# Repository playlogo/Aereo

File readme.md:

# Aereo - CO2 & PM2.5 Air Sensor with custom PCB

A DIY IoT air-quality sensor using a `Senseair S8` for CO2 and a `PMS5003` for particulate matter.

Features:

- ESP32c3 firmware to publish measurements to influxDB
- Custom PCB for easy assembly
- Grafana dashboard to display data

|||
|-|-|
|||

## Tutorial

### Installing InfluxDB & Grafana using docker

1. Clone this repo: `git clone https://github.com/playlogo/Aereo.git`
2. Run `docker compose up -d`

3. Setup Grafana at: `http://<ip>:3000`
4. Setup InfluxDB at: `http://<ip>:8086`

5. Follow [this guide](https://www.influxdata.com/blog/getting-started-influxdb-grafana/) to add InfluxDB as a Datasource to Grafana
6. Import the Grafana dashboard:
    - Create a new empty dashboard: `Home` -> `Dashboards` -> `New`
    - Click the little gear icon to get to the `Dashboard Settings`
    - Go to the `JSON Model` tab
    - Copy the contents of the `grafana_dashboard.json` file and paste them into the editor
    - Hit `Save Changes` and reload - voilà (you might still need to change the Datasource of each Graph to the one you just created)

Optional: Create your own dashboard following the guide linked above (don't forget to hit save!)

### Flashing the ESP32c3

1. Open `.vscode/Aereo.code-workspace` using VSCode, make sure you have [PlatformIO](https://platformio.org/install/ide?install=vscode) installed and setup
2. Create `Aereo/src/secrets.h` with the following content:

```cpp
#define WIFI_SSID "NEIGHBORS_WIFI"
#define WIFI_PASSWORD "123456789"

#define INFLUXDB_URL "http://192.168.178.64:8086/"
#define INFLUXDB_TOKEN "token please" // Guide: https://docs.influxdata.com/influxdb3/cloud-serverless/admin/tokens/create-token/
#define INFLUXDB_ORG "bumble"
#define INFLUXDB_BUCKET "aereo" // Guide: https://docs.influxdata.com/influxdb/v2/admin/buckets/create-bucket/
```

3. Build & Upload to the ESP32c3: `CTRL+P` -> `PlatformIO: Upload`
4. The neopixel should blink blue while the ESP connects to wifi, when connected it should turn off - if it continues showing one static color, one of the sensors has not been detected -> Check serial output: `CTRL+P` -> `PlatformIO: Upload and Monitor`

## Hardware

Required components:

- `ENS160-AHT21`: Temp + TVOC sensor ~4€ on aliexpress
- `Senseair S8`: [NDIR](https://en.wikipedia.org/wiki/Nondispersive_infrared_sensor) CO2 Sensor ~20€ on aliexpress
- `PMS5003`:  Particulate matter sensor ~14€ on aliexpress
- `WeAct ESP32C3 CoreBoard`: ~4€ on aliexpress
- `SK6812 mini e`: 1x ARGB status LED ~3€ on aliexpress (for 100pcs)

PCB:

- Houses two independent projects to save costs, the right half can simply be ignored
- Exposed connectors:
  - 2x 3 Pin (5V, GND, Data)
  - 2x 4 Pin (5V, GND, Data, Data)
  - 3x Power (5V, GND)
- Size: 100x100mm

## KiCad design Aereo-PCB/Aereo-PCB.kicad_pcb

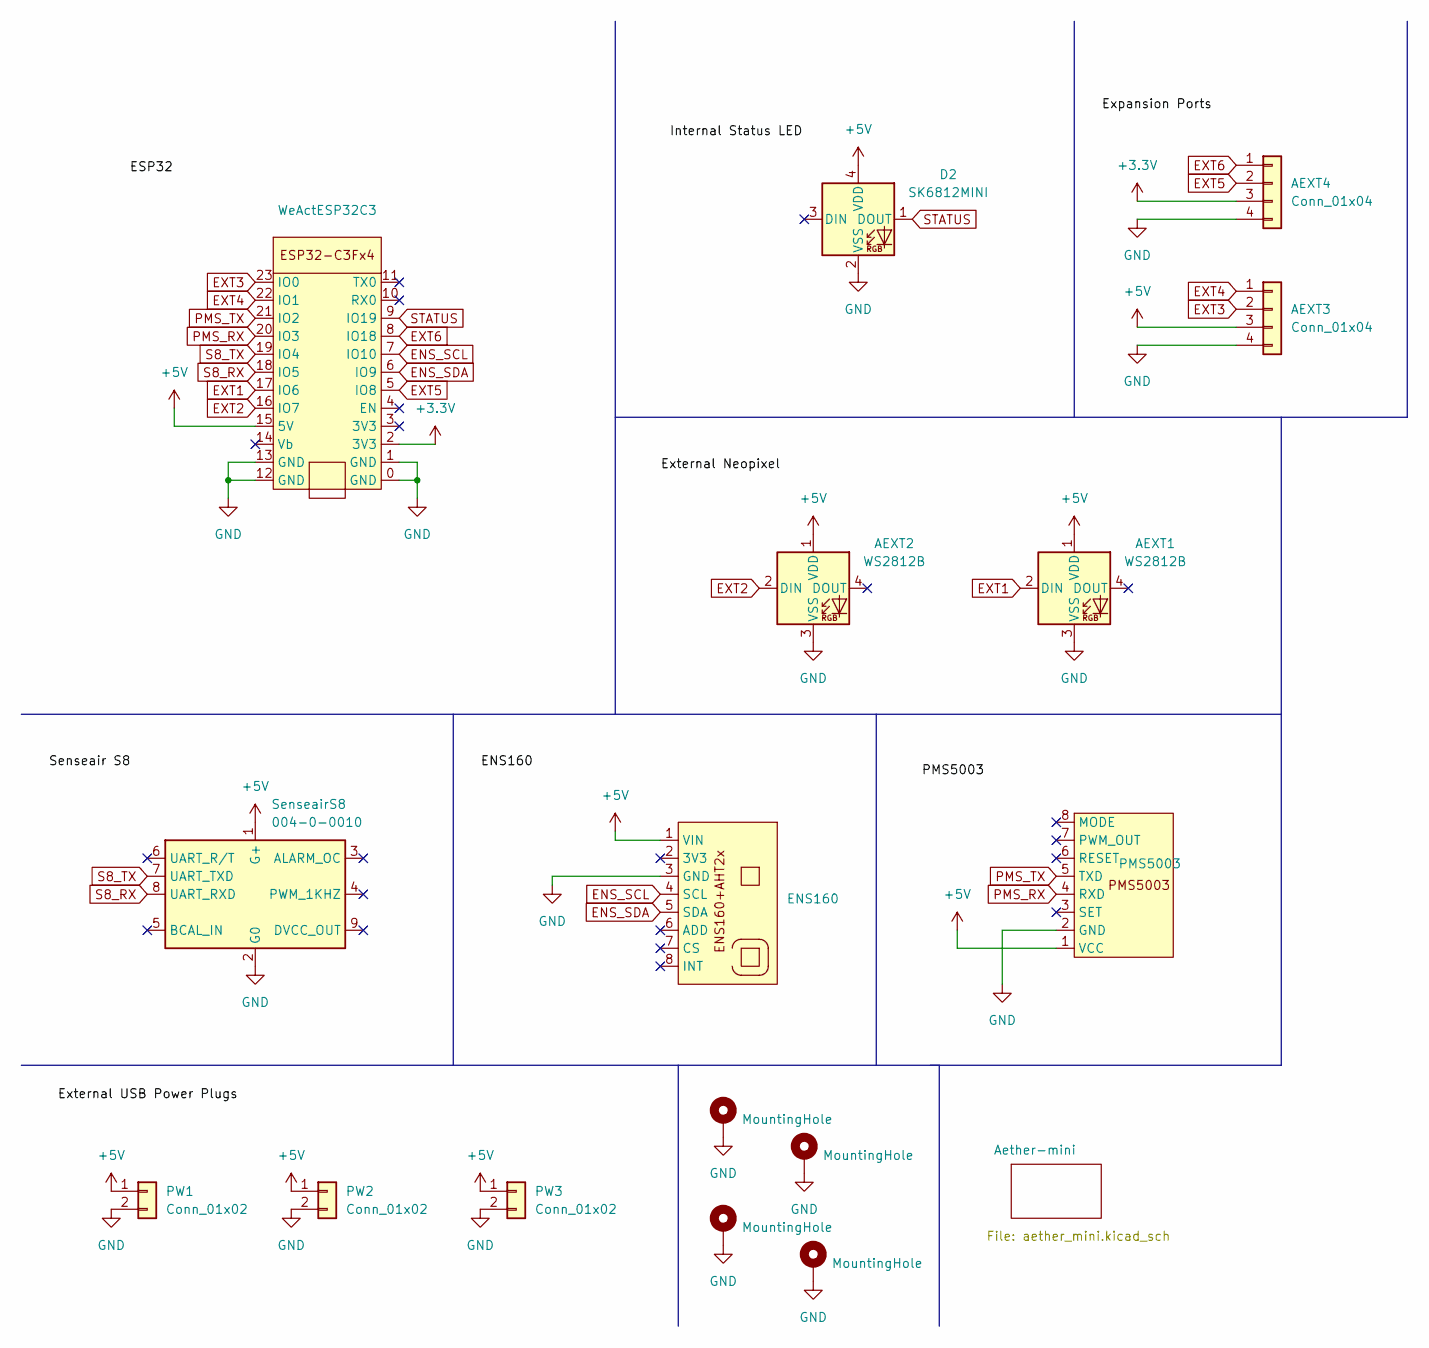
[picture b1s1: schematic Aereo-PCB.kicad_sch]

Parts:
AEXT1, AEXT2: WS2812B; JST_XH_B3B-XH-A_1x03_P2.50mm_Vertical
AEXT3, AEXT4: Conn_01x04; JST_XH_B4B-XH-A_1x04_P2.50mm_Vertical
D2: SK6812MINI; LED_SK6812MINI_PLCC4_3.5x3.5mm_P1.75mm
ENS160: PinHeader_1x08_P2.54mm_Vertical
H1, H2, H3, H4: MountingHole; MountingHole_3.2mm_M3_DIN965_Pad
PMS5003: JST_XH_B5B-XH-A_1x05_P2.50mm_Vertical
PW1, PW2, PW3: Conn_01x02; JST_PH_B2B-PH-K_1x02_P2.00mm_Vertical
SenseairS8: 004-0-0010; Senseair_S8_Down
WeActESP32C3: WeAct ESP32-C3Fx4 Core mini

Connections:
+3.3V: AEXT4.3, WeActESP32C3.2 (3V3)
+5V: AEXT1.1 (VDD), AEXT2.1 (VDD), AEXT3.3, D2.4 (VDD), ENS160.1 (VIN), PMS5003.1 (VCC), PW1.1, PW2.1, PW3.1, SenseairS8.1 (G+), WeActESP32C3.15 (5V)
ENS_SCL: ENS160.4 (SCL), WeActESP32C3.7 (IO10)
ENS_SDA: ENS160.5 (SDA), WeActESP32C3.6 (IO9)
EXT1: AEXT1.2 (DIN), WeActESP32C3.17 (IO6)
EXT2: AEXT2.2 (DIN), WeActESP32C3.16 (IO7)
EXT3: AEXT3.2, WeActESP32C3.23 (IO0)
EXT4: AEXT3.1, WeActESP32C3.22 (IO1)
EXT5: AEXT4.2, WeActESP32C3.5 (IO8)
EXT6: AEXT4.1, WeActESP32C3.8 (IO18)
GND: AEXT1.3 (VSS), AEXT2.3 (VSS), AEXT3.4, AEXT4.4, D2.2 (VSS), ENS160.3 (GND), H1.1, H2.1, H3.1, H4.1, PMS5003.2 (GND), PW1.2, PW2.2, PW3.2, SenseairS8.2 (G0), WeActESP32C3.0 (GND), WeActESP32C3.1 (GND), WeActESP32C3.12 (GND), WeActESP32C3.13 (GND); also elsewhere on the board
PMS_RX: PMS5003.4 (RXD), WeActESP32C3.20 (IO3)
PMS_TX: PMS5003.5 (TXD), WeActESP32C3.21 (IO2)
S8_RX: SenseairS8.8 (UART_RXD), WeActESP32C3.18 (IO5)
S8_TX: SenseairS8.7 (UART_TXD), WeActESP32C3.19 (IO4)
STATUS: D2.1 (DOUT), WeActESP32C3.9 (IO19)

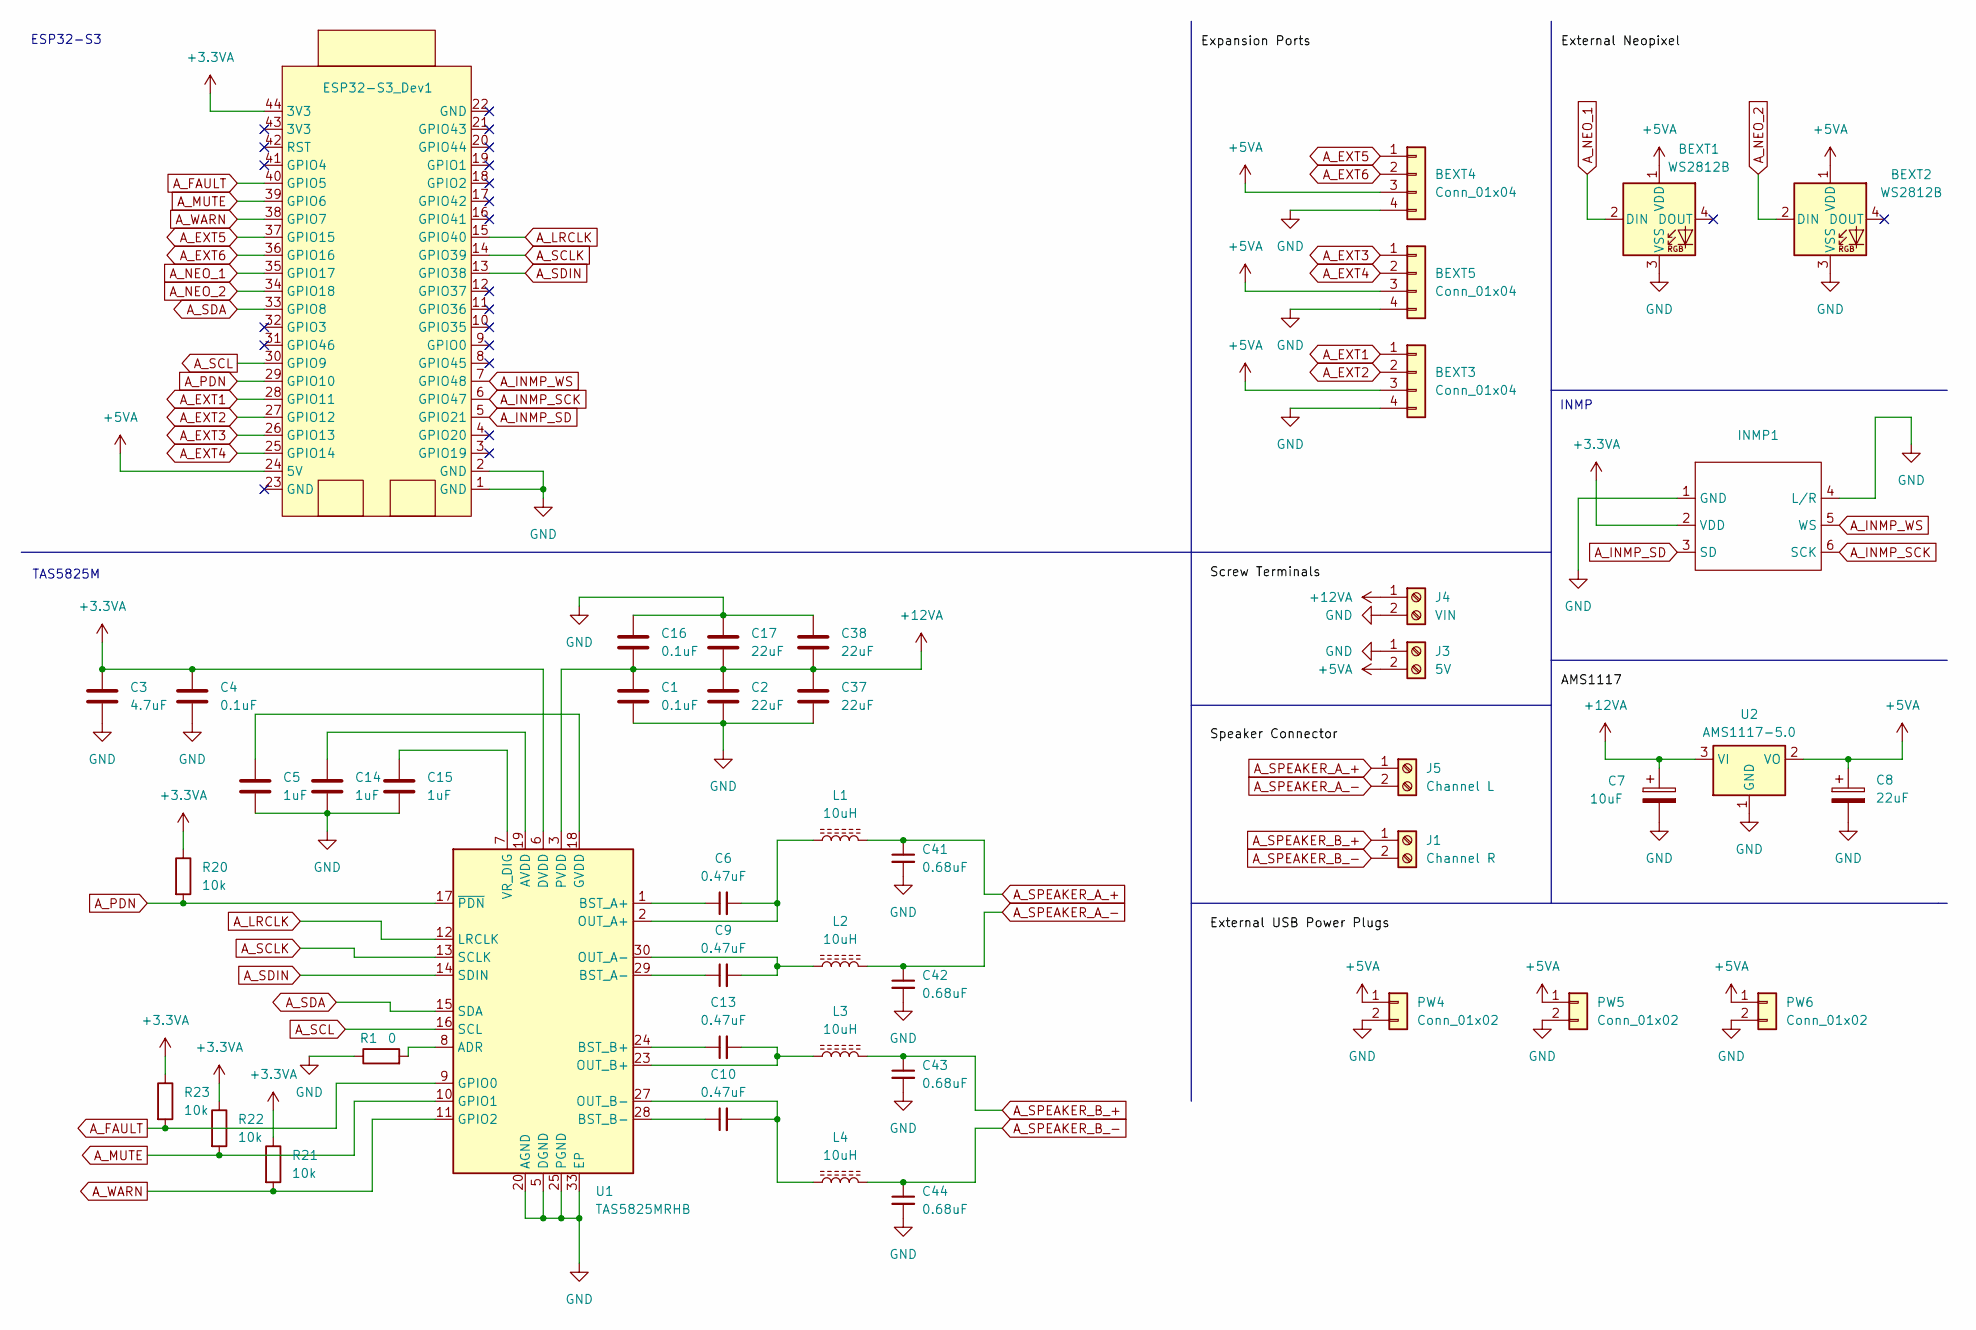
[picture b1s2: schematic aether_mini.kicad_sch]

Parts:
BEXT1, BEXT2: WS2812B; JST_XH_B3B-XH-A_1x03_P2.50mm_Vertical
BEXT3, BEXT4, BEXT5: Conn_01x04; JST_XH_B4B-XH-A_1x04_P2.50mm_Vertical
C1, C4, C16: 0.1uF; C_0805_2012Metric_Pad1.18x1.45mm_HandSolder
C2, C8, C17, C37, C38: 22uF; C_0805_2012Metric_Pad1.18x1.45mm_HandSolder
C3: 4.7uF; C_0805_2012Metric_Pad1.18x1.45mm_HandSolder
C5, C14, C15: 1uF; C_0805_2012Metric_Pad1.18x1.45mm_HandSolder
C6, C9, C10, C13: 0.47uF; C_0805_2012Metric_Pad1.18x1.45mm_HandSolder
C7: 10uF; C_0805_2012Metric_Pad1.18x1.45mm_HandSolder
C41, C42, C43, C44: 0.68uF; C_0805_2012Metric_Pad1.18x1.45mm_HandSolder
ESP32-S3_Dev1: ESP32-S3-Dev
INMP1: INMP441
J1: Channel R; JWT_A3963_1x02_P3.96mm_Vertical
J3: 5V; JWT_A3963_1x02_P3.96mm_Vertical
J4: VIN; JWT_A3963_1x02_P3.96mm_Vertical
J5: Channel L; JWT_A3963_1x02_P3.96mm_Vertical
L1, L2, L3, L4: 10uH; L_10.4x10.4_H4.8
PW4, PW5, PW6: Conn_01x02; JST_PH_B2B-PH-K_1x02_P2.00mm_Vertical
R1: 0; R_0805_2012Metric_Pad1.20x1.40mm_HandSolder
R20, R21, R22, R23: 10k; R_0805_2012Metric_Pad1.20x1.40mm_HandSolder
U1: TAS5825MRHB; VQFN-32-1EP_5x5mm_P0.5mm_EP3.1x3.1mm
U2: AMS1117-5.0; SOT-223-3_TabPin2

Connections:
+3.3VA: C3.1, C4.1, ESP32-S3_Dev1.44 (3V3), INMP1.2 (VDD), R20.1, R21.1, R22.1, R23.1, U1.6 (DVDD)
+5VA: BEXT1.1 (VDD), BEXT2.1 (VDD), BEXT3.3, BEXT4.3, BEXT5.3, C8.1, ESP32-S3_Dev1.24 (5V), J3.2, PW4.1, PW5.1, PW6.1, U2.2 (VO)
+12VA: C1.1, C2.1, C7.1, C16.2, C17.2, C37.1, C38.2, J4.1, U1.3 (PVDD), U1.4 (PVDD), U1.21 (PVDD), U1.22 (PVDD), U2.3 (VI)
A_EXT1: BEXT3.1, ESP32-S3_Dev1.28 (GPIO11)
A_EXT2: BEXT3.2, ESP32-S3_Dev1.27 (GPIO12)
A_EXT3: BEXT5.1, ESP32-S3_Dev1.26 (GPIO13)
A_EXT4: BEXT5.2, ESP32-S3_Dev1.25 (GPIO14)
A_EXT5: BEXT4.1, ESP32-S3_Dev1.37 (GPIO15)
A_EXT6: BEXT4.2, ESP32-S3_Dev1.36 (GPIO16)
A_FAULT: ESP32-S3_Dev1.40 (GPIO5), R23.2, U1.9 (GPIO0)
A_INMP_SCK: ESP32-S3_Dev1.6 (GPIO47), INMP1.6 (SCK)
A_INMP_SD: ESP32-S3_Dev1.5 (GPIO21), INMP1.3 (SD)
A_INMP_WS: ESP32-S3_Dev1.7 (GPIO48), INMP1.5 (WS)
A_LRCLK: ESP32-S3_Dev1.15 (GPIO40), U1.12 (LRCLK)
A_MUTE: ESP32-S3_Dev1.39 (GPIO6), R22.2, U1.10 (GPIO1)
A_NEO_1: BEXT1.2 (DIN), ESP32-S3_Dev1.35 (GPIO17)
A_NEO_2: BEXT2.2 (DIN), ESP32-S3_Dev1.34 (GPIO18)
A_PDN: ESP32-S3_Dev1.29 (GPIO10), R20.2, U1.17 (~PDN)
A_SCL: ESP32-S3_Dev1.30 (GPIO9), U1.16 (SCL)
A_SCLK: ESP32-S3_Dev1.14 (GPIO39), U1.13 (SCLK)
A_SDA: ESP32-S3_Dev1.33 (GPIO8), U1.15 (SDA)
A_SDIN: ESP32-S3_Dev1.13 (GPIO38), U1.14 (SDIN)
A_SPEAKER_A_+: C41.1, J5.1, L1.2
A_SPEAKER_A_-: C42.1, J5.2, L2.2
A_SPEAKER_B_+: C43.1, J1.1, L3.2
A_SPEAKER_B_-: C44.1, J1.2, L4.2
A_WARN: ESP32-S3_Dev1.38 (GPIO7), R21.2, U1.11 (GPIO2)
GND: BEXT1.3 (VSS), BEXT2.3 (VSS), BEXT3.4, BEXT4.4, BEXT5.4, C1.2, C2.2, C3.2, C4.2, C5.2, C7.2, C8.2, C14.2, C15.2, C16.1, C17.1, C37.2, C38.1, C41.2, C42.2, C43.2, C44.2, ESP32-S3_Dev1.1 (GND), ESP32-S3_Dev1.2 (GND), INMP1.1 (GND), INMP1.4 (L/R), J3.1, J4.2, PW4.2, PW5.2, PW6.2, R1.1, U1.5 (DGND), U1.20 (AGND), U1.25 (PGND), U1.26 (PGND), U1.31 (PGND), U1.32 (PGND), U1.33 (EP), U2.1 (GND); also elsewhere on the board
unnamed: R1.2, U1.8 (ADR)
unnamed: C14.1, U1.19 (AVDD)
unnamed: C6.1, U1.1 (BST_A+)
unnamed: C9.1, U1.29 (BST_A-)
unnamed: C13.1, U1.24 (BST_B+)
unnamed: C10.1, U1.28 (BST_B-)
unnamed: C5.1, U1.18 (GVDD)
unnamed: C6.2, L1.1, U1.2 (OUT_A+)
unnamed: C9.2, L2.1, U1.30 (OUT_A-)
unnamed: C13.2, L3.1, U1.23 (OUT_B+)
unnamed: C10.2, L4.1, U1.27 (OUT_B-)
unnamed: C15.1, U1.7 (VR_DIG)

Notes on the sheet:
ESP32-S3
INMP
TAS5825M

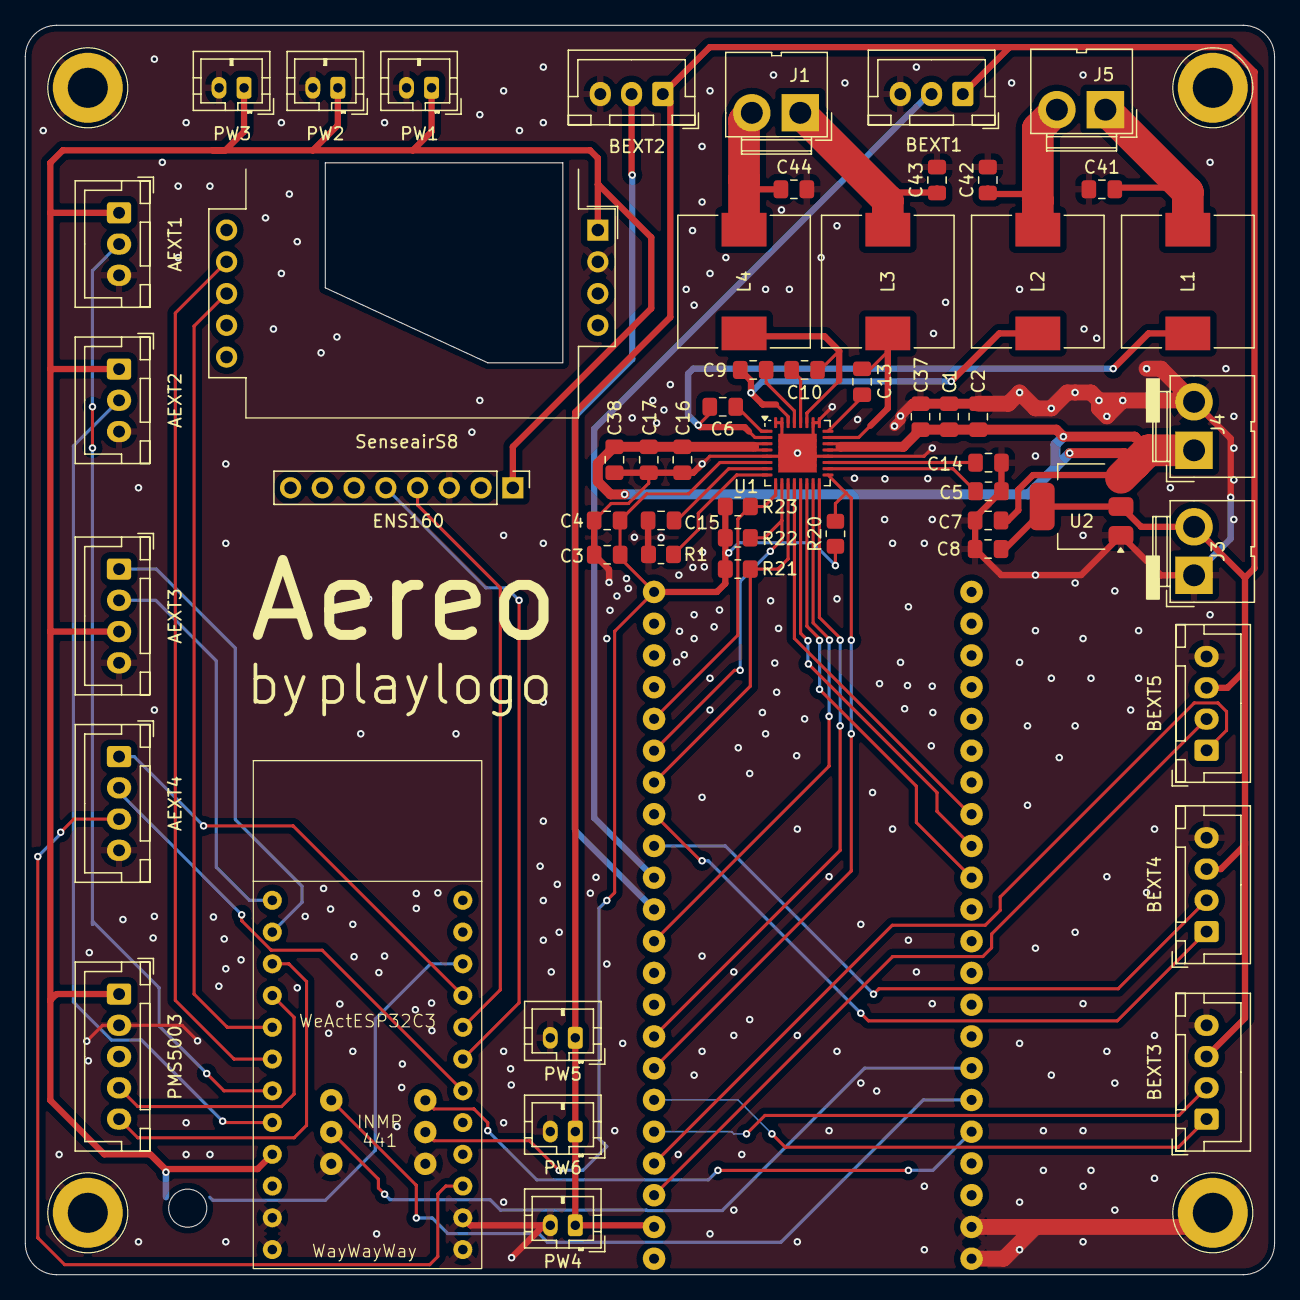
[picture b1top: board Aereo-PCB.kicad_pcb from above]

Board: 2 copper layers, 99.9 x 99.9 mm, 62 parts (1 on the bottom side), 55 nets.

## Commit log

2024-11-18 Initial prototype
2024-11-18 Working influx db logger
2024-11-19 Added senseair s8 sensor!
2024-11-19 Splitting the code into modules, tons of small tweaks
2024-11-19 Changed tmp type to floats, add support for custom pins for I2C
2024-11-20 Small improvements, cleanup
2025-01-30 Added Custom PCB, added debug neopixel
2025-01-30 Added images
2025-01-31 Improved documentation
